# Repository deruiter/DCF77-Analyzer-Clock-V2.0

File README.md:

DCF77 Analyzer/Clock v2.0

 This sketch is free software; you can redistribute it and/or
 modify it under the terms of the GNU Lesser General Public
 License as published by the Free Software Foundation; either
 version 2.1 of the License, or (at your option) any later version.
 
 This sketch is distributed in the hope that it will be useful,
 but WITHOUT ANY WARRANTY; without even the implied warranty of
 MERCHANTABILITY or FITNESS FOR A PARTICULAR PURPOSE.  See the GNU
 Lesser General Public License for more details.
 
 You should have received a copy of the GNU Lesser General Public
 License along with this library; if not, write to the Free Software
 Foundation, Inc., 51 Franklin St, Fifth Floor, Boston, MA  02110-1301  USA

 This C++ code is far from optimized because I myself am an Arduino and C++ novice.
 But even after learning some more now, I want to keep the code simpel and readable.
 That is why I maybe over-documented the code to help understand what's going on.

 Erik de Ruiter
 2014-2016

 May 2014 First version
 March 2016 - big overhaul...
 July 2016 - Start with building the v2.0 Clock and adapting the sketch

 Version 2.0 - August 2016
 - This sketch is adapted for my 2.0 version of the DCF/Analyzer Clock. It used the Arduino MEGA and the DCF Superfilter
   by default and to drive the many seperate LED's I now use the ports of an Arduino Mega instead of a Maxim 7219 chip. 
   This is because driving LED's with many different Voltage/Current specs is problematic with the Maxim chip. 
   Lighting additional LED's for expample will influence (dim) the LED's already on. As I'm not an electronics engineer
   my only solution was to use the extra ports of the Arduino Mega. Ofcourse you can use transistors or extra chips to
   drive the LED's but for me this was the obvious solution.
 - Removed all the code to use Maxim 72xx chips with Common Anode displays

                                                                                                                                                                                                                                                                                                                                                                                                                                                                                                                                                                                                                                                                                                                                                                                                                                                                                                                                                                                                                                                                                                                                                                                                                                                                                                                                                                                                                                                                                                                                                                                                                                                                                                                                                                                                                                                                                                                                                                                                                                                                                                                                                                                                                                                                                                                                                                                                                                                                                                                                                                                                                                                                                                                                                                                                                                                                                                                                                                                                                                                                                                                                                                                                                                                                                                                                                                                                                                                                                                                                                                                                                                                                                                                                                            

 Version 1.72 - May 2016
 - Option: Use a cheap Ebay PIR detector to shut off selectable display's when no activity is detected. 
   The switch off delay can be set by the user to prevent the display shutting of if a person
   is not moving but the display should be on.
 - Now the display Night shut-down can be disabled by making both values 'POWERSAVINGOFFTIME'
   and 'POWERSAVINGONTIME' zero. 
 - Fixed temperature display not shutting off at powersave mode.  
 - errorCounter display did not reset every hour so that's fixed

 Version 1.71
 - User option to reset temperature min/max memory at midnight

 Version 1.7:
 - The resolution of the temperature display is improved: from 0.5 to 0.1 degrees Celsius
   Because of the time the DS18B20 sensor needs to convert the temperature and to keep the code clean, 
   the temperature display is updates once per minute.
 - Parity check routine optimized. 
 - More reliable check for bad DCF data, preventing RTC update with invalid data.
 - EoB error now clears inner LED ring as it should.
 - The DCF OK LED now displays the condition of the DCF signal more reliably. Turns off immediately if an error occurs
   and only turns ON when all 3 parity bits are OK.

 Version 1.6:
 - Changed temperature function to only calculate once per minute. Got strange errors before the change because
   I used a delay of 100ms to give the DS18B20 sensor time to calculate the temperature. But the delay function is
   a very bad idea in most c++ code so I finally got rid of it.

 Version 1.5:
 - Complete overhaul of the scanSignal function and the rest of the code! My first attempt worked but could be improved...
 - The rPW and rPT led's did not work as I intended so that is corrected now.
 - The End of Buffer error check routine does work now as it should.
 - I incorporated a Parity check of the incoming DCF signal. In the signal 3 Parity bits are sent so now these are
   checked and only if all three are OK, the received time information is accepted, the display is updated and the RTC synced.
   if desired, you can attach 3 extra dual-color LED's (Common Cathode) to see if each of the 3 Parity bits are OK or Failed.
 - I made wiring (or changing the wiring) much easier I think by putting all the PIN config in one easy to read table
 - As long as you use 1 DS18B20 temp. sensor, I edited the code so you no longer need to figure out the address of the I2C device.
 - Big clean-up of the code...
 - Powersaving by shutting off the displays (the clock remains functioning as normal)
   can now be configured somewhat easier by editing two variables POWERSAVINGONTIME and POWERSAVINGOFFTIME.
 - changed some variable names:
   - Maxim instances 'lc' and 'lc1' are now MaximCC and MaximCA
   - Display description MaximDcfTime is now DisplayTempWeek 
   - DCF77SOUNDPIN is now BUZZERSWITCHPIN
 - LED/Display test after power up now build in

  Short description:
   
  Power On:
    After power-on, first a LED test is performed. The LED's and displays lite up sequentially to keep the power consumption low.
    Then the clock starts receiving DCF pulses and when a Minute Mark (2 seconds gap) is detected, the Minute Marker LED is lit
    and the buffer counter is reset. The inner LED ring now will show the incoming DCF pulses which are also stored in the buffer.
    At 3 moments during reception of data the parity DCF bits are checked to see if the data is valid.

  Valid data received:
    When, at the end of the minute, after the Minute Mark is detected (BF (Buffer Full) LED is lit), all three parity bits are OK
    ('DCF OK' LED is lit), the buffer information is used to extract time and date information. 
    Then the RTC clock is updated ('RTC Synced' LED is lit) and the inner LED ring information is copied to the outer LED ring. 
    The time, date and week display, day LED, summer/wintertime and leap year LED information is updated with the new time information.

  No valid data:
    When one or more of the parity bits are not OK because of a noisy signal, receiving of DCF information is continued but
    will not be used to update the RTC, display's and LED's. The outer LED ring, 'RTC synced' and 'DCF OK' LED's will be reset. 
    Time, date, week, day LED, summer/wintertime LED and leap year LED are not affected and keep displaying the last received valid values.
    The 'Period Time' and/or 'Period With' error LED's will indicate the error(s) and the error counter display is updated. 
    Every hour, the error display will bet set to zero. 
    The EoB, End of Buffer LED is lit when more DCF pulses are received before the Minute Mark is detected due to a noisy signal.
    (When a minute Mark is detected we should have no more than 58 bits/pulses) 
    After the detection of the Minute Marker, a new cycle is started.
 
  Temperature:
    At the 30 second mark, the temperature display will show the High and Low values of the past period after the last reset.
  
  Chime:
    At the beginning of each hour, the Chime (if connected) will sound. 
    At night time, a time set by the user in the code itself, the chime is disabled.

  Power saving, two options:
    1. NIGHT SHUT OFF
       At times set by the user, the displays are shutt off at night and turned on in the morning.
       Look at the POWERSAVINGOFFTIME and POWERSAVINGONTIME variables. 
       Check the function <turnDisplaysOff> to select which displays you want to shut off at night.
    2. PIR SENSOR
       Connect a PIR sensor and activate the PIR option POWERSAVE_BY_PIR and the the delay at PIR_DELAY_TIME.
       Every time the PIR detector senses movement, a minute counter is reset but if no movement is detected
       longer than the PIR_DELAY_TIME, the displays are shut off. 
       When movement occurs, the displays immediately switch on. 
    Note: as said before, the clock will function normally while the displays are shut off. 
    The only thing is you can't see it... ;)

  DCF beep:
    With a switch, connected to pin BUZZERSWITCHPIN, you can hear the received DCF bits coming in. 
    The tone duration is equivalent to pulse width of the DCF bits, so either 100 or 200 ms.
  
  Miscelleanous:
    When the RTC battery is empty or a connection fault is detected, the RTC Error LED is lit.

 CREDITS:
 I learned a lot from the work of Matthias Dalheimer and Thijs Elenbaas who made their own DCF77 decoders.
 Without their work I would not have known where to start.
 I ended up writing my own code (using bits and pieces of their ideas) so I could understand what is happening...
 My code is far from efficient or advanced but it does work and I know what is going on.
 
 * A big Thank You to Brett Oliver and Joop Tap for pointing out some errors!

 Interesting websites:

 - Brett Oliver         : http://home.btconnect.com/brettoliver1/
 - Joop Tap             : http://www.jooptap.nl
 - Thijs Ellenbaas      : http://thijs.elenbaas.net/2012/04/arduino-dcf77-radio-clock-receiver-hardware-2/
 - Mathias Dalheimer    : https://github.com/roddi/DCF77-Arduino/blob/master/DCF77Servoclock/DCF77.h
 - DCF77 wikipedia      : https://en.wikipedia.org/wiki/DCF77
 - Much more DCF77 info : http://www.picbasic.nl/indexes_uk.htm

 - My Flickr website    : https://www.flickr.com/photos/edr1924/albums
 - My Github website    : https://github.com/deruiter
 - The Instructables website for this clock: soon!

 */

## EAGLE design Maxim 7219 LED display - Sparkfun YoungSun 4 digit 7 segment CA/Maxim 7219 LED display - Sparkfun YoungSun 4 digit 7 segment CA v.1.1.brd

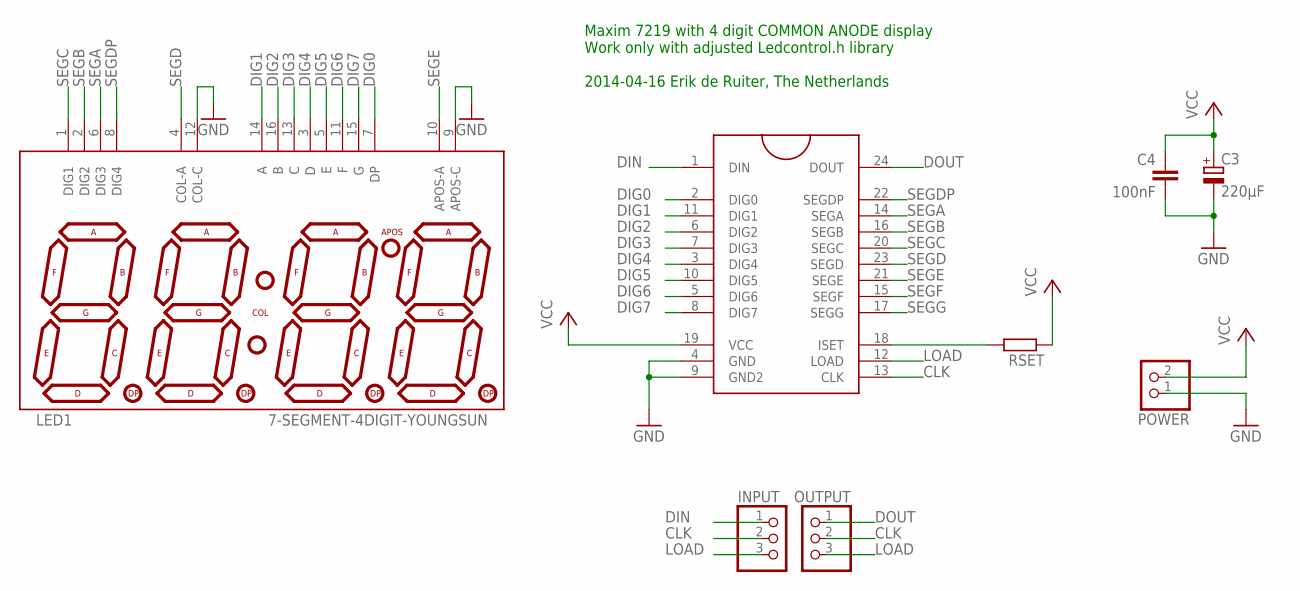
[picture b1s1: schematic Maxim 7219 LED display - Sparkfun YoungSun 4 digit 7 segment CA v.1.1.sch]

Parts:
C3: 220µF; E3,5-8
C4: 100nF; C050-025X075
INPUT: PINHD-1X3; 1X03
LED1: 7-SEGMENT-4DIGIT-YOUNGSUN
OUTPUT: PINHD-1X3; 1X03
POWER: PINHD-1X2; 1X02
RSET: R-EU_0207/10; 0207/10
U$3: MAX7219DIP; DIL24

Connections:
CLK: INPUT.2, OUTPUT.2, U$3.13 (CLK)
DIG0: LED1.7 (DP), U$3.2 (DIG0)
DIG1: LED1.14 (A), U$3.11 (DIG1)
DIG2: LED1.16 (B), U$3.6 (DIG2)
DIG3: LED1.13 (C), U$3.7 (DIG3)
DIG4: LED1.3 (D), U$3.3 (DIG4)
DIG5: LED1.5 (E), U$3.10 (DIG5)
DIG6: LED1.11 (F), U$3.5 (DIG6)
DIG7: LED1.15 (G), U$3.8 (DIG7)
DIN: INPUT.1, U$3.1 (DIN)
DOUT: OUTPUT.1, U$3.24 (DOUT)
GND: C3.-, C4.2, LED1.9 (APOS-C), LED1.12 (COL-C), POWER.1, U$3.4 (GND), U$3.9 (GND2)
LOAD: INPUT.3, OUTPUT.3, U$3.12 (LOAD)
unnamed: RSET.2, U$3.18 (ISET)
SEGA: LED1.6 (DIG3), U$3.14 (SEGA)
SEGB: LED1.2 (DIG2), U$3.16 (SEGB)
SEGC: LED1.1 (DIG1), U$3.20 (SEGC)
SEGD: LED1.4 (COL-A), U$3.23 (SEGD)
SEGDP: LED1.8 (DIG4), U$3.22 (SEGDP)
SEGE: LED1.10 (APOS-A), U$3.21 (SEGE)
SEGF: U$3.15 (SEGF)
SEGG: U$3.17 (SEGG)
VCC: C3.+, C4.1, POWER.2, RSET.1, U$3.19 (VCC)

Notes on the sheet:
Maxim 7219 with 4 digit COMMON ANODE display Work only with adjusted Ledcontrol.h library 2014-04-16 Erik de Ruiter, The Netherlands

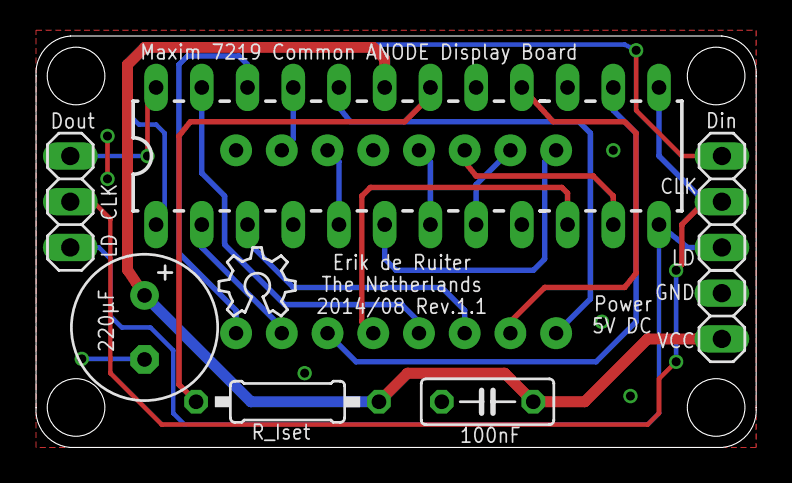
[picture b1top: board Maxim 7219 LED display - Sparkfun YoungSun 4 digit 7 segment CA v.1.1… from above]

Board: 2 copper layers, 40.0 x 22.9 mm, 9 parts (1 on the bottom side), 21 nets.

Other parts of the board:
U$2: OSHW_6X150_NOTEXT

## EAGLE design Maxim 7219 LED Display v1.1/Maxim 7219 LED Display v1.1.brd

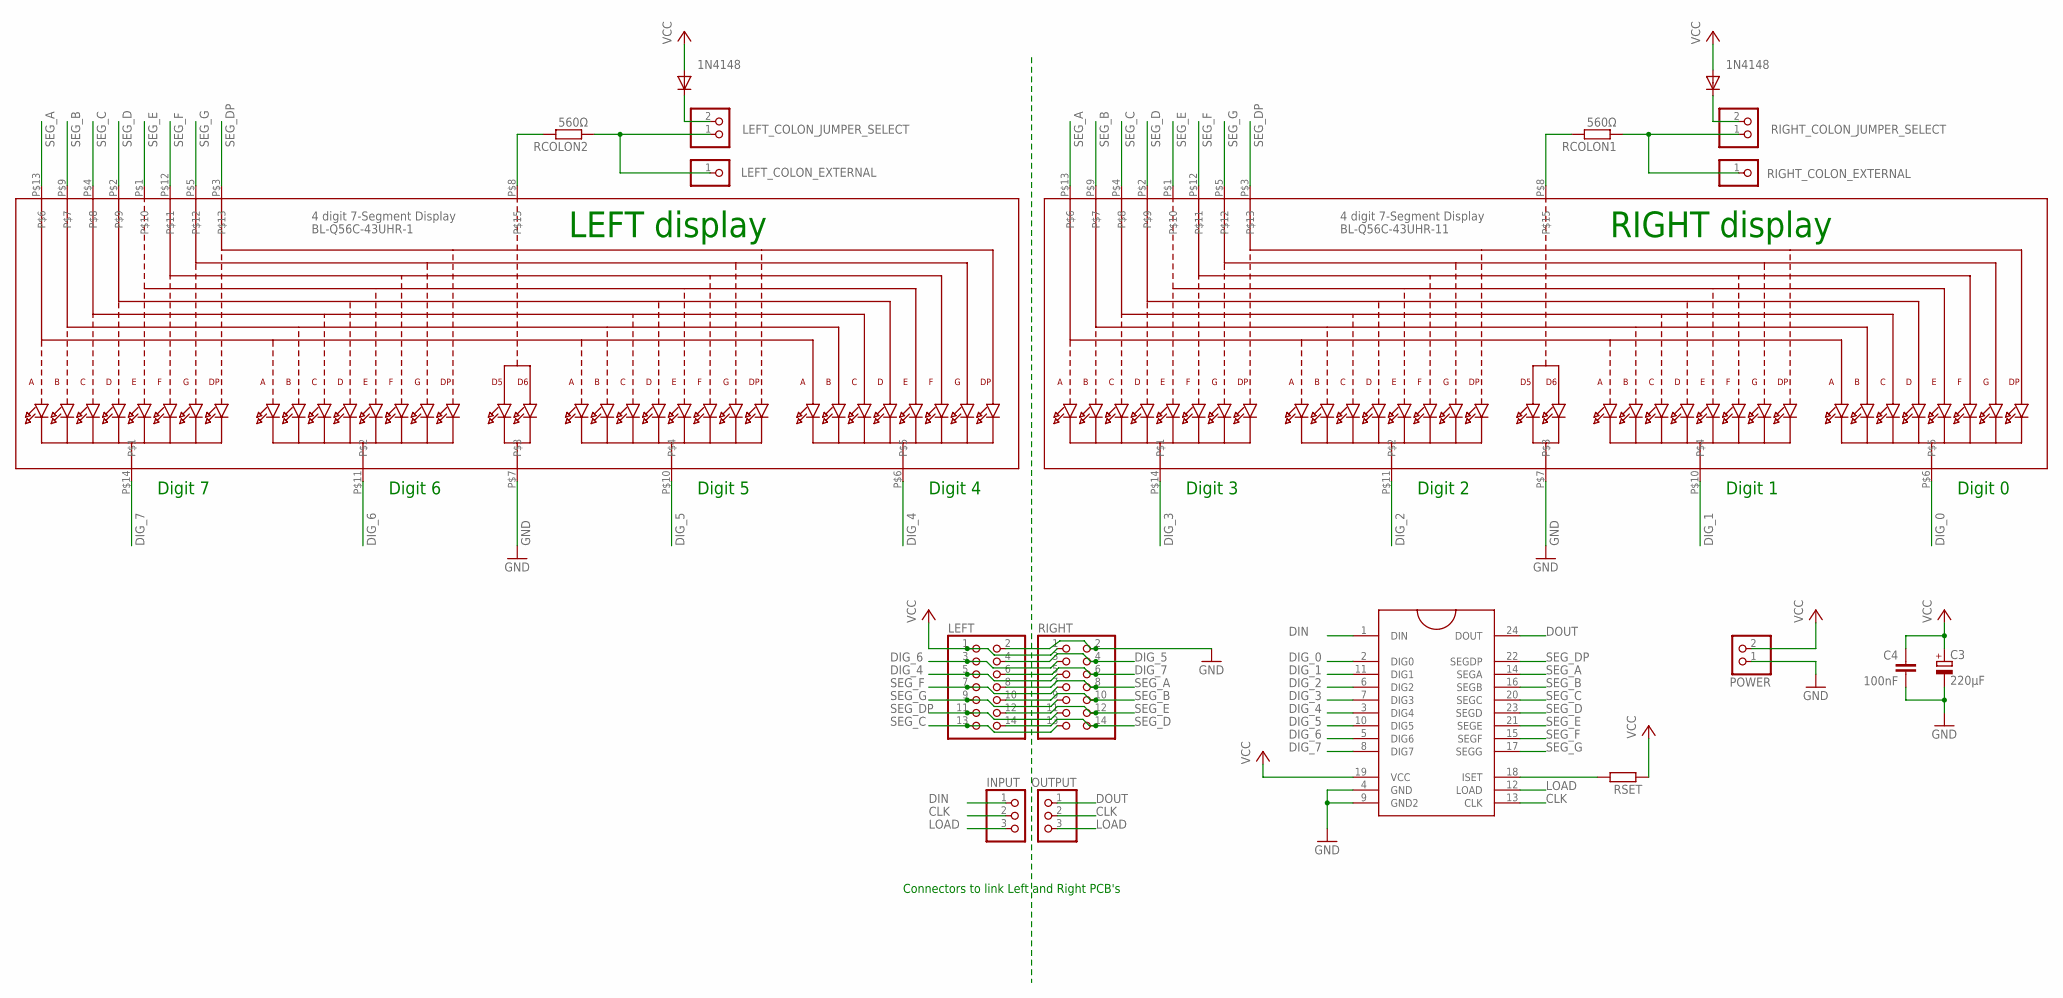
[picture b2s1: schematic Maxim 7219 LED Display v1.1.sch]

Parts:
BL-Q56C-43UHR-1, BL-Q56C-43UHR-11: 4 digit 7-Segment Display; SEGMENT-BL-Q56C43
C3: 220µF; E5-10,5
C4: 100nF; C050-025X075
D2, D3: 1N4148; DO35-7
INPUT: PINHD-1X3; 1X03
LEFT: PINHD-2X7; 2X07
LEFT_COLON_EXTERNAL: M01SMDNS; 1X01
LEFT_COLON_JUMPER_SELECT: PINHD-1X2; 1X02
OUTPUT: PINHD-1X3; 1X03
POWER: PINHD-1X2; 1X02
RCOLON1, RCOLON2: 560Ω; 0207/10
RIGHT: PINHD-2X7; 2X07
RIGHT_COLON_EXTERNAL: PINHD-1X1; 1X01
RIGHT_COLON_JUMPER_SELECT: PINHD-1X2; 1X02
RSET: R-EU_0207/2V; 0207/2V
U$3: MAX7219DIP; DIL24

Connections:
CLK: INPUT.2, OUTPUT.2, U$3.13 (CLK)
DIG_0: BL-Q56C-43UHR-11.P$6, U$3.2 (DIG0)
DIG_1: BL-Q56C-43UHR-11.P$10, U$3.11 (DIG1)
DIG_2: BL-Q56C-43UHR-11.P$11, U$3.6 (DIG2)
DIG_3: BL-Q56C-43UHR-11.P$14, U$3.7 (DIG3)
DIG_4: BL-Q56C-43UHR-1.P$6, LEFT.5, RIGHT.5, U$3.3 (DIG4)
DIG_5: BL-Q56C-43UHR-1.P$10, LEFT.4, RIGHT.4, U$3.10 (DIG5)
DIG_6: BL-Q56C-43UHR-1.P$11, LEFT.3, RIGHT.3, U$3.5 (DIG6)
DIG_7: BL-Q56C-43UHR-1.P$14, LEFT.6, RIGHT.6, U$3.8 (DIG7)
DIN: INPUT.1, U$3.1 (DIN)
DOUT: OUTPUT.1, U$3.24 (DOUT)
GND: BL-Q56C-43UHR-1.P$7, BL-Q56C-43UHR-11.P$7, C3.-, C4.2, LEFT.2, POWER.1, RIGHT.2, U$3.4 (GND), U$3.9 (GND2)
LOAD: INPUT.3, OUTPUT.3, U$3.12 (LOAD)
unnamed: D2.C, LEFT_COLON_JUMPER_SELECT.2
unnamed: LEFT_COLON_EXTERNAL.1, LEFT_COLON_JUMPER_SELECT.1, RCOLON2.1
unnamed: BL-Q56C-43UHR-1.P$8, RCOLON2.2
unnamed: BL-Q56C-43UHR-11.P$8, RCOLON1.2
unnamed: D3.C, RIGHT_COLON_JUMPER_SELECT.2
unnamed: RCOLON1.1, RIGHT_COLON_EXTERNAL.1, RIGHT_COLON_JUMPER_SELECT.1
unnamed: RSET.2, U$3.18 (ISET)
SEG_A: BL-Q56C-43UHR-1.P$13, BL-Q56C-43UHR-11.P$13, LEFT.8, RIGHT.8, U$3.14 (SEGA)
SEG_B: BL-Q56C-43UHR-1.P$9, BL-Q56C-43UHR-11.P$9, LEFT.10, RIGHT.10, U$3.16 (SEGB)
SEG_C: BL-Q56C-43UHR-1.P$4, BL-Q56C-43UHR-11.P$4, LEFT.13, RIGHT.13, U$3.20 (SEGC)
SEG_D: BL-Q56C-43UHR-1.P$2, BL-Q56C-43UHR-11.P$2, LEFT.14, RIGHT.14, U$3.23 (SEGD)
SEG_DP: BL-Q56C-43UHR-1.P$3, BL-Q56C-43UHR-11.P$3, LEFT.11, RIGHT.11, U$3.22 (SEGDP)
SEG_E: BL-Q56C-43UHR-1.P$1, BL-Q56C-43UHR-11.P$1, LEFT.12, RIGHT.12, U$3.21 (SEGE)
SEG_F: BL-Q56C-43UHR-1.P$12, BL-Q56C-43UHR-11.P$12, LEFT.7, RIGHT.7, U$3.15 (SEGF)
SEG_G: BL-Q56C-43UHR-1.P$5, BL-Q56C-43UHR-11.P$5, LEFT.9, RIGHT.9, U$3.17 (SEGG)
VCC: C3.+, C4.1, D2.A, D3.A, LEFT.1, POWER.2, RIGHT.1, RSET.1, U$3.19 (VCC)

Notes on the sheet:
LEFT display
RIGHT display
Connectors to link Left and Right PCB's
Digit 0
Digit 1
Digit 2
Digit 3
Digit 4
Digit 5
Digit 6
Digit 7

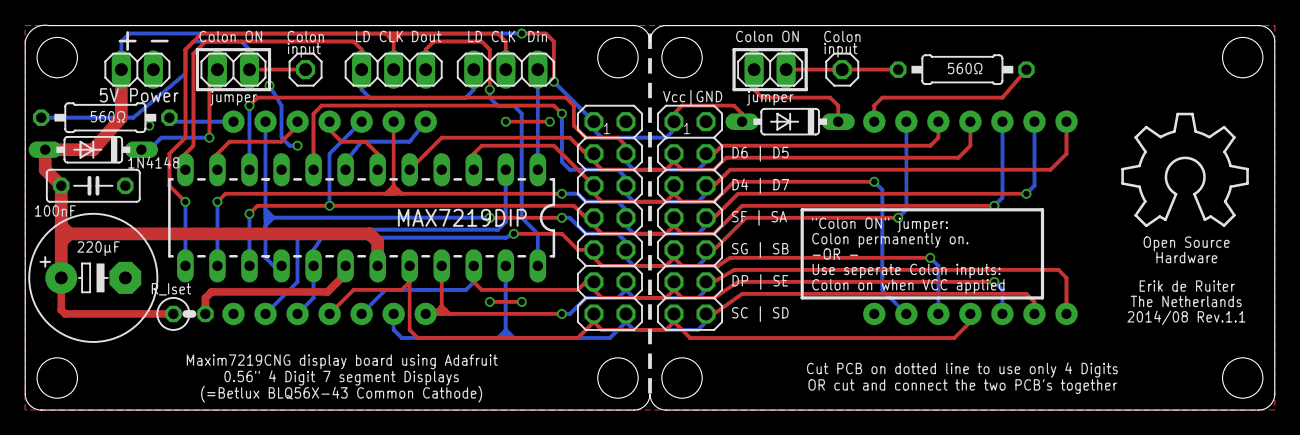
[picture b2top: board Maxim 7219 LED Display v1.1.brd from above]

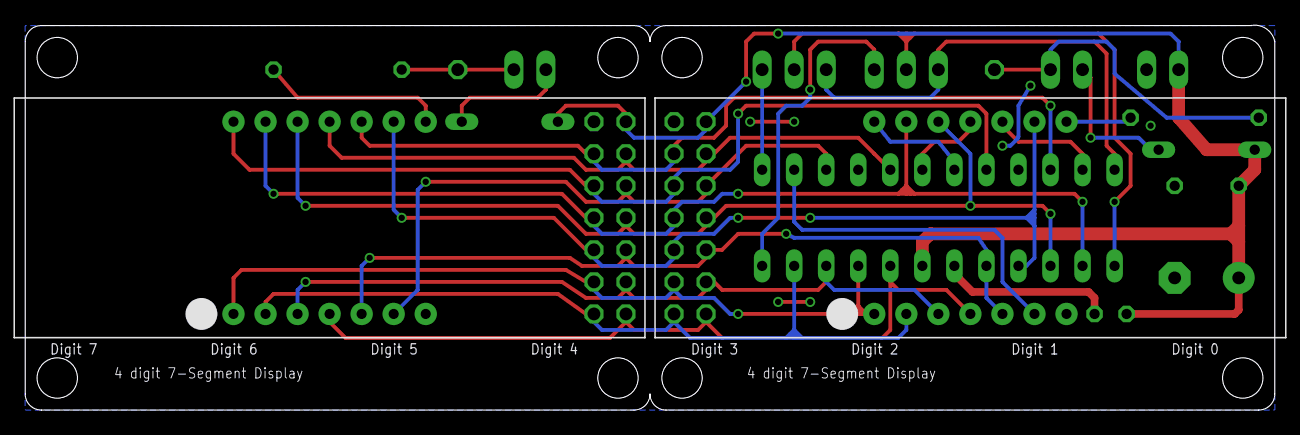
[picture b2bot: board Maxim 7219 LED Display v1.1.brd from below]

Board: 2 copper layers, 99.1 x 30.5 mm, 20 parts (2 on the bottom side), 29 nets.

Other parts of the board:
U$2: OSHW_8X350_NOTEXT

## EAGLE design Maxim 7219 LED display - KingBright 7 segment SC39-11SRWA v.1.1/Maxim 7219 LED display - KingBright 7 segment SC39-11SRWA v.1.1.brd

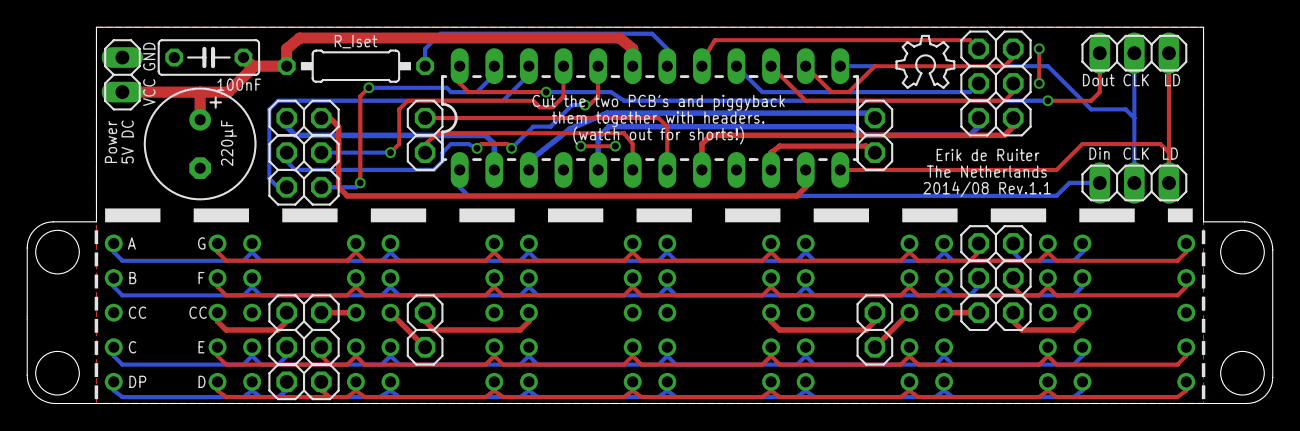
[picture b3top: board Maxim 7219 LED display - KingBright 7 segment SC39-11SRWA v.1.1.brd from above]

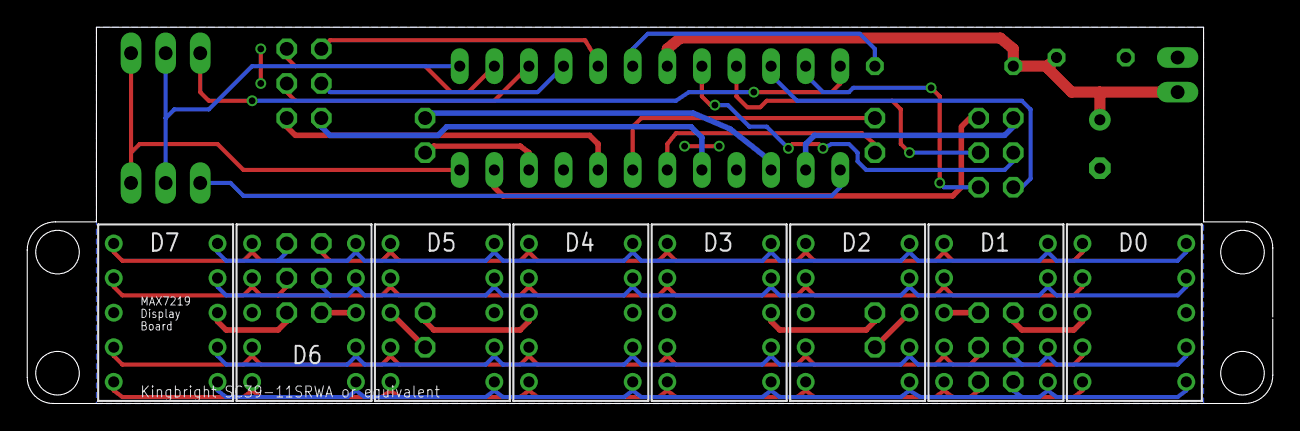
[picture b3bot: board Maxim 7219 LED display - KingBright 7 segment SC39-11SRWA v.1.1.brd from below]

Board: 2 copper layers, 91.4 x 27.6 mm, 48 parts (8 on the bottom side), 39 nets.

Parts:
C3: 220µF; E3,5-8
C4: 100nF; C050-025X075
D0, D1, D2, D3, D4, D5, D6, D7: SC39-11SRWA; HDSP-E
DIG_0_D, DIG_0_M, DIG_1_D, DIG_1_M, DIG_2_D, DIG_2_M, DIG_3_D, DIG_3_M, DIG_4_D, DIG_4_M, DIG_5_D, DIG_5_M, DIG_6_D, DIG_6_M, DIG_7_D, DIG_7_M: 1X01
INPUT: 1X03
OUTPUT: 1X03
POWER: 1X02
RSET: 0207/10
SEG_A_D: 1X01
SEG_A_M: 1X01
SEG_B_D: 1X01
SEG_B_M: 1X01
SEG_C_D: 1X01
SEG_C_M: 1X01
SEG_DP_D: 1X01
SEG_DP_M: 1X01
SEG_D_D: 1X01
SEG_D_M: 1X01
SEG_E_D: 1X01
SEG_E_M: 1X01
SEG_F_D: 1X01
SEG_F_M: 1X01
SEG_G_D: 1X01
SEG_G_M: 1X01
U$2: OSHW_6X150_NOTEXT
U$3: MAX7219DIP; DIL24

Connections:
CLK: INPUT.2, OUTPUT.2, U$3.13
DIG0: DIG_0_M.1, U$3.2
DIG1: DIG_1_M.1, U$3.11
DIG2: DIG_2_M.1, U$3.6
DIG3: DIG_3_M.1, U$3.7
DIG4: DIG_4_M.1, U$3.3
DIG5: DIG_5_M.1, U$3.10
DIG6: DIG_6_M.1, U$3.5
DIG7: DIG_7_M.1, U$3.8
DIG_0: D0.3, DIG_0_D.1
DIG_1: D1.3, DIG_1_D.1
DIG_2: D2.8, DIG_2_D.1
DIG_3: D3.8, DIG_3_D.1
DIG_4: D4.3, DIG_4_D.1
DIG_5: D5.3, DIG_5_D.1
DIG_6: D6.8, DIG_6_D.1
DIG_7: D7.8, DIG_7_D.1
DIN: INPUT.1, U$3.1
DOUT: OUTPUT.1, U$3.24
GND: C3.-, C4.2, POWER.1, U$3.4, U$3.9
LOAD: INPUT.3, OUTPUT.3, U$3.12
unnamed: RSET.2, U$3.18
SEGA: SEG_A_M.1, U$3.14
SEGB: SEG_B_M.1, U$3.16
SEGC: SEG_C_M.1, U$3.20
SEGD: SEG_D_M.1, U$3.23
SEGDP: SEG_DP_M.1, U$3.22
SEGE: SEG_E_M.1, U$3.21
SEGF: SEG_F_M.1, U$3.15
SEGG: SEG_G_M.1, U$3.17
SEG_A: D0.10, D1.10, D2.10, D3.10, D4.10, D5.10, D6.10, D7.10, SEG_A_D.1
SEG_B: D0.9, D1.9, D2.9, D3.9, D4.9, D5.9, D6.9, D7.9, SEG_B_D.1
SEG_C: D0.7, D1.7, D2.7, D3.7, D4.7, D5.7, D6.7, D7.7, SEG_C_D.1
SEG_D: D0.5, D1.5, D2.5, D3.5, D4.5, D5.5, D6.5, D7.5, SEG_D_D.1
SEG_DP: D0.6, D1.6, D2.6, D3.6, D4.6, D5.6, D6.6, D7.6, SEG_DP_D.1
SEG_E: D0.4, D1.4, D2.4, D3.4, D4.4, D5.4, D6.4, D7.4, SEG_E_D.1
SEG_F: D0.2, D1.2, D2.2, D3.2, D4.2, D5.2, D6.2, D7.2, SEG_F_D.1
SEG_G: D0.1, D1.1, D2.1, D3.1, D4.1, D5.1, D6.1, D7.1, SEG_G_D.1
VCC: C3.+, C4.1, POWER.2, RSET.1, U$3.19

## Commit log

2014-08-22 Added Eagle files
2014-08-22 moved to folder
2014-08-22 Revert "moved to folder"
    This reverts commit 2a864635d2108374a6d6668000cdb38c7414912c.
2014-08-22 Display Board Eagle files
2014-08-22 Eagle Cad Display Board
2014-08-22 MODIFIED Ledcontrol library
    With this library, you can use Common ANODE displays if you want with
    the Maxim 72xx chips!
2014-08-22 Photo of DCF77 Clock
2015-03-20 Added credits ;)
2015-03-22 Schematic added, finally!
2015-03-23 Added other schematic versions
2016-03-09 BIG overhaul
    Major rewrite of the complete sketch!
2016-03-09 updated version
2016-03-09 layout edit
2016-05-21 UPDATE
    addes some useful options (I think…)
2016-05-21 Update
    Updated with net 1.72 info
2016-05-21 minor edit
2016-08-01 DCF77-Analyzer-Clock-v2
2019-08-13 fixed leap year error

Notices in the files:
parts and their libraries:
SparkFun-DigitalIC: Licensing: CC v3.0 Share-Alike You are welcome to use this library for commercial purposes.
